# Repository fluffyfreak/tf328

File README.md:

# TF328 Revision 1

An 8mb Fast RAM + IDE Board for the CD32.

Known Issues: 

1. Your CF Card MUST be 3.3/5V tolerant as some of the control signals are 3.3V.

A prototype version was built and this contains all the lessons learned from that prototype. 

This repository contains all the files needed to produce a copy of my IDE+RAM board.

The CPLDs Required are 1 x XC9572XL-10VQ64 and 1 x XC9536XL-10VQG44C.  10ns "Commercial" version is fine.

Everything in this repository is released under the GNU GPLv2. You may create or base commercial PCBs from the work in this repository but you must make the sources for all derivative work available. I have noticed some forks have removed copyright notices. This is a breach of the GPL.

## Board Options

### Clock Buffer 

The clock buffer is a stabilty modification I added to buffer the clock due to slow rise times observed on other Amiga Hardware. It may not be required at all. If you decide not to add the clock buffer then you should jumper the middle pin of the CLOCKSEL jumper to the pin nearest the edge connector. If you wish to use the buffered clock you need to add IC9 and jumper the middle pin to the position nearest the IDE connector. If you wish to disable the board remove the jumper entirely.

### External Power

Jumper PWR1 is intended for use when bringing up the board so that the CPLDs can be programmed without inserting the card. It is not required after this unless you wish to use it to power other devices. 

### JMP Feature 

Jumper JMP is intended to trigger an NMI. This works via the MUXCPLD which detects the external pin being pulled HIGH and will pull IPL0-2 low until released. This feature is done synchronously to prevent glitches. It is intended for use with HRTMon. 

## Firmware / Requirements

  * Xilinx ISE, 14.7 (the final version - other versions may work but this is the one I support)
  * JTAG Adaptor

[For more information visit my channel](https://www.youtube.com/c/TerribleFire)

## License

This project and all the files contained are released under the GNU GPLv2. If you build a modified version of the board you must supply the end user with all the sources (this can be a web link).

# Bill of Materials

|Part | Value | Device | Package | Description |
|-----|-------|--------|---------|-------------|
| R1 | 1K | RESISTOR1206 | 1206 | Resistors | 
| R2 | 1K | RESISTOR1206 | 1206 | Resistors | 
| C1 | 10uF | CAP_CERAMIC1206 | 1206 | Ceramic Capacitors | 
| C2 | 10uF | CAP_CERAMIC1206 | 1206 | Ceramic Capacitors | 
| C3 | 10uF | CAP_CERAMIC1206 | 1206 | Ceramic Capacitors | 
| C4 | 22uF | CAP_CERAMIC1206 | 1206 | Ceramic Capacitors | 
| C5 | 100nF | CAP_CERAMIC1206 | 1206 | Ceramic Capacitors | 
| C6 | 22uF | CAP_CERAMIC1206 | 1206 | Ceramic Capacitors | 
| C7 | 1uF | CAP_CERAMIC1206 | 1206 | Ceramic Capacitors | 
| C8 | 100nF | CAP_CERAMIC1206 | 1206 | Ceramic Capacitors | 
| C9 | 100nF | CAP_CERAMIC1206 | 1206 | Ceramic Capacitors | 
| C10 | 10uF | CAP_CERAMIC1206 | 1206 | Ceramic Capacitors | 
| C11 | 22uF | CAP_CERAMIC1206 | 1206 | Ceramic Capacitors | 
| C12 | 22uF | CAP_CERAMIC1206 | 1206 | Ceramic Capacitors | 
| C13 | 22uF | CAP_CERAMIC1206 | 1206 | Ceramic Capacitors | 
| C14 | 100nF | CAP_CERAMIC1206 | 1206 | Ceramic Capacitors | 
| C15 | 100nF | CAP_CERAMIC1206 | 1206 | Ceramic Capacitors | 
| C16 | 1uF | CC0603 | C0603 | CAPACITOR, European symbol | 
| IC1 | IS41C16100C | IS41C16100C | TSOP44(50)-II |   |
| IC2 | IS41C16100C | IS41C16100C | TSOP44(50)-II |   |
| IC3 | IS41C16100C | IS41C16100C | TSOP44(50)-II |   |
| IC4 | IS41C16100C | IS41C16100C | TSOP44(50)-II |   |
| IC5 | LM1117-3.3 | V_REG_LM1117SOT223 | SOT223 | Voltage Regulator LM1117 |
| IC9 | 74LVC1G17DBV | 74LVC1G17DBV | SOT23-5 | Single Schmitt-Trigger Buffer (Optional)| 
| JMP | Optional | JUMPER-2PTH | 1X02 | NMI Jumper | 
| JP1 | CLOCKSEL | JUMPER-3PTH | 1X03 |        | 
| JTAG | JTAG | HEADER-1X6ROUND | 1X06_ROUND | PIN HEADER | 
| PWR1 | EXT5V | JUMPER-2PTH | 1X02 | Jumper | 
| MUXCPLD | XC9536XL-10VQG44C | XC9536XL-10VQG44C | SQFP-S-10X10-44 | xc9536_pc44 XC9500 In-System Programmable CPLD Family | 
| RAMCPLD | XC9572XL-10VQ64 | XC9572XL-10VQ64 | VQ64 |  
| IDECONNECTOR | 87758-4416 | 87758-4416 | 87758-4416 | 44 Pin - 2mm Dual Row Single Wafer, Vertical T/H HDR |

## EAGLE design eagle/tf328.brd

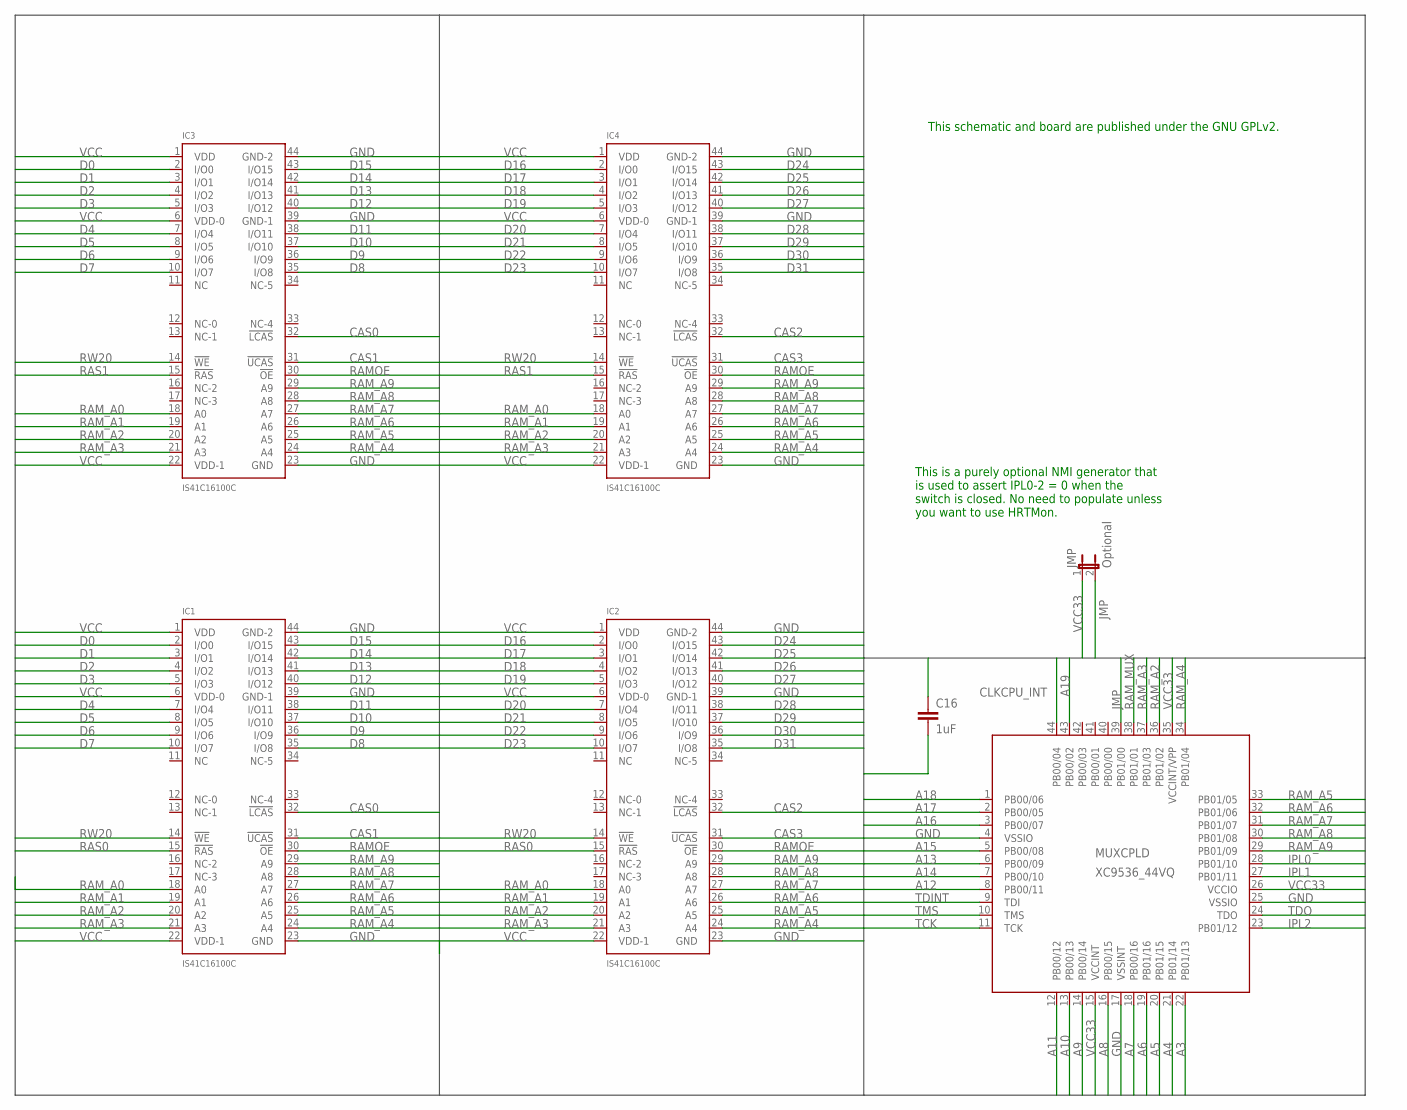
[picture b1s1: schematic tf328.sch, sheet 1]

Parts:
C16: 1uF; C0603
IC1, IC2, IC3, IC4: IS41C16100C; TSOP44(50)-II
JMP: Optional; 1X02
MUXCPLD: XC9536_44VQ; SQFP-S-10X10-44

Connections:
A3: MUXCPLD.22 (PB01/13); also elsewhere on the board
A4: MUXCPLD.21 (PB01/14); also elsewhere on the board
A5: MUXCPLD.20 (PB01/15); also elsewhere on the board
A6: MUXCPLD.19 (PB01/16); also elsewhere on the board
A7: MUXCPLD.18 (PB00/16); also elsewhere on the board
A8: MUXCPLD.16 (PB00/15); also elsewhere on the board
A9: MUXCPLD.14 (PB00/14); also elsewhere on the board
A10: MUXCPLD.13 (PB00/13); also elsewhere on the board
A11: MUXCPLD.12 (PB00/12); also elsewhere on the board
A12: MUXCPLD.8 (PB00/11); also elsewhere on the board
A13: MUXCPLD.6 (PB00/09); also elsewhere on the board
A14: MUXCPLD.7 (PB00/10); also elsewhere on the board
A15: MUXCPLD.5 (PB00/08); also elsewhere on the board
A16: MUXCPLD.3 (PB00/07); also elsewhere on the board
A17: MUXCPLD.2 (PB00/05); also elsewhere on the board
A18: MUXCPLD.1 (PB00/06); also elsewhere on the board
A19: MUXCPLD.43 (PB00/02); also elsewhere on the board
CAS0: IC1.32 (!LCAS), IC3.32 (!LCAS); also elsewhere on the board
CAS1: IC1.31 (!UCAS), IC3.31 (!UCAS); also elsewhere on the board
CAS2: IC2.32 (!LCAS), IC4.32 (!LCAS); also elsewhere on the board
CAS3: IC2.31 (!UCAS), IC4.31 (!UCAS); also elsewhere on the board
CLKCPU_INT: MUXCPLD.44 (PB00/04); also elsewhere on the board
D0: IC1.2 (I/O0), IC3.2 (I/O0); also elsewhere on the board
D1: IC1.3 (I/O1), IC3.3 (I/O1); also elsewhere on the board
D2: IC1.4 (I/O2), IC3.4 (I/O2); also elsewhere on the board
D3: IC1.5 (I/O3), IC3.5 (I/O3); also elsewhere on the board
D4: IC1.7 (I/O4), IC3.7 (I/O4); also elsewhere on the board
D5: IC1.8 (I/O5), IC3.8 (I/O5); also elsewhere on the board
D6: IC1.9 (I/O6), IC3.9 (I/O6); also elsewhere on the board
D7: IC1.10 (I/O7), IC3.10 (I/O7); also elsewhere on the board
D8: IC1.35 (I/O8), IC3.35 (I/O8); also elsewhere on the board
D9: IC1.36 (I/O9), IC3.36 (I/O9); also elsewhere on the board
D10: IC1.37 (I/O10), IC3.37 (I/O10); also elsewhere on the board
D11: IC1.38 (I/O11), IC3.38 (I/O11); also elsewhere on the board
D12: IC1.40 (I/O12), IC3.40 (I/O12); also elsewhere on the board
D13: IC1.41 (I/O13), IC3.41 (I/O13); also elsewhere on the board
D14: IC1.42 (I/O14), IC3.42 (I/O14); also elsewhere on the board
D15: IC1.43 (I/O15), IC3.43 (I/O15); also elsewhere on the board
D16: IC2.2 (I/O0), IC4.2 (I/O0); also elsewhere on the board
D17: IC2.3 (I/O1), IC4.3 (I/O1); also elsewhere on the board
D18: IC2.4 (I/O2), IC4.4 (I/O2); also elsewhere on the board
D19: IC2.5 (I/O3), IC4.5 (I/O3); also elsewhere on the board
D20: IC2.7 (I/O4), IC4.7 (I/O4); also elsewhere on the board
D21: IC2.8 (I/O5), IC4.8 (I/O5); also elsewhere on the board
D22: IC2.9 (I/O6), IC4.9 (I/O6); also elsewhere on the board
D23: IC2.10 (I/O7), IC4.10 (I/O7); also elsewhere on the board
D24: IC2.43 (I/O15), IC4.43 (I/O15); also elsewhere on the board
D25: IC2.42 (I/O14), IC4.42 (I/O14); also elsewhere on the board
D26: IC2.41 (I/O13), IC4.41 (I/O13); also elsewhere on the board
D27: IC2.40 (I/O12), IC4.40 (I/O12); also elsewhere on the board
D28: IC2.38 (I/O11), IC4.38 (I/O11); also elsewhere on the board
D29: IC2.37 (I/O10), IC4.37 (I/O10); also elsewhere on the board
D30: IC2.36 (I/O9), IC4.36 (I/O9); also elsewhere on the board
D31: IC2.35 (I/O8), IC4.35 (I/O8); also elsewhere on the board
GND: C16.2, IC1.23 (GND), IC1.39 (GND-1), IC1.44 (GND-2), IC2.23 (GND), IC2.39 (GND-1), IC2.44 (GND-2), IC3.23 (GND), IC3.39 (GND-1), IC3.44 (GND-2), IC4.23 (GND), IC4.39 (GND-1), IC4.44 (GND-2), MUXCPLD.4 (VSSIO), MUXCPLD.17 (VSSINT), MUXCPLD.25 (VSSIO); also elsewhere on the board
IPL0: MUXCPLD.28 (PB01/10); also elsewhere on the board
IPL1: MUXCPLD.27 (PB01/11); also elsewhere on the board
IPL2: MUXCPLD.23 (PB01/12); also elsewhere on the board
JMP: JMP.2, MUXCPLD.39 (PB01/00)
RAMOE: IC1.30 (!OE), IC2.30 (!OE), IC3.30 (!OE), IC4.30 (!OE); also elsewhere on the board
RAM_A0: IC1.18 (A0), IC2.18 (A0), IC3.18 (A0), IC4.18 (A0); also elsewhere on the board
RAM_A1: IC1.19 (A1), IC2.19 (A1), IC3.19 (A1), IC4.19 (A1); also elsewhere on the board
RAM_A2: IC1.20 (A2), IC2.20 (A2), IC3.20 (A2), IC4.20 (A2), MUXCPLD.36 (PB01/02)
RAM_A3: IC1.21 (A3), IC2.21 (A3), IC3.21 (A3), IC4.21 (A3), MUXCPLD.37 (PB01/03)
RAM_A4: IC1.24 (A4), IC2.24 (A4), IC3.24 (A4), IC4.24 (A4), MUXCPLD.34 (PB01/04)
RAM_A5: IC1.25 (A5), IC2.25 (A5), IC3.25 (A5), IC4.25 (A5), MUXCPLD.33 (PB01/05)
RAM_A6: IC1.26 (A6), IC2.26 (A6), IC3.26 (A6), IC4.26 (A6), MUXCPLD.32 (PB01/06)
RAM_A7: IC1.27 (A7), IC2.27 (A7), IC3.27 (A7), IC4.27 (A7), MUXCPLD.31 (PB01/07)
RAM_A8: IC1.28 (A8), IC2.28 (A8), IC3.28 (A8), IC4.28 (A8), MUXCPLD.30 (PB01/08)
RAM_A9: IC1.29 (A9), IC2.29 (A9), IC3.29 (A9), IC4.29 (A9), MUXCPLD.29 (PB01/09)
RAM_MUX: MUXCPLD.38 (PB01/01); also elsewhere on the board
RAS0: IC1.15 (!RAS), IC2.15 (!RAS); also elsewhere on the board
RAS1: IC3.15 (!RAS), IC4.15 (!RAS); also elsewhere on the board
RW20: IC1.14 (!WE), IC2.14 (!WE), IC3.14 (!WE), IC4.14 (!WE); also elsewhere on the board
TCK: MUXCPLD.11 (TCK); also elsewhere on the board
TDINT: MUXCPLD.9 (TDI); also elsewhere on the board
TDO: MUXCPLD.24 (TDO); also elsewhere on the board
TMS: MUXCPLD.10 (TMS); also elsewhere on the board
VCC: IC1.1 (VDD), IC1.6 (VDD-0), IC1.22 (VDD-1), IC2.1 (VDD), IC2.6 (VDD-0), IC2.22 (VDD-1), IC3.1 (VDD), IC3.6 (VDD-0), IC3.22 (VDD-1), IC4.1 (VDD), IC4.6 (VDD-0), IC4.22 (VDD-1); also elsewhere on the board
VCC33: C16.1, JMP.1, MUXCPLD.15 (VCCINT), MUXCPLD.26 (VCCIO), MUXCPLD.35 (VCCINT/VPP); also elsewhere on the board

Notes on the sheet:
This is a purely optional NMI generator that is used to assert IPL0-2 = 0 when the switch is closed. No need to populate unless you want to use HRTMon.
This schematic and board are published under the GNU GPLv2.

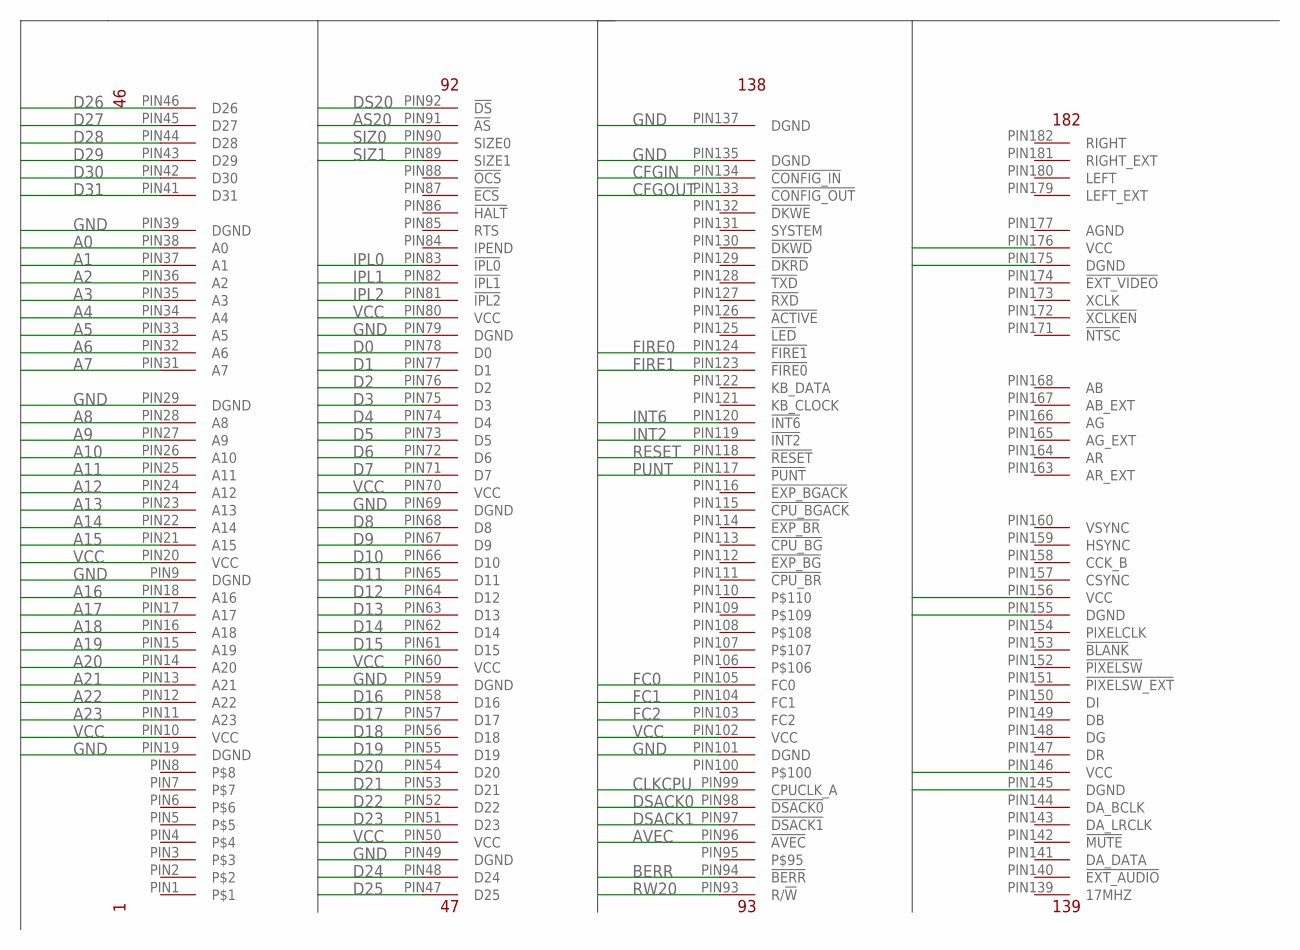
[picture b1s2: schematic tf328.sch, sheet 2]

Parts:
CONN1: MCA_CONN_182

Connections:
A0: CONN1.PIN38 (A0); also elsewhere on the board
A1: CONN1.PIN37 (A1); also elsewhere on the board
A2: CONN1.PIN36 (A2); also elsewhere on the board
A3: CONN1.PIN35 (A3); also elsewhere on the board
A4: CONN1.PIN34 (A4); also elsewhere on the board
A5: CONN1.PIN33 (A5); also elsewhere on the board
A6: CONN1.PIN32 (A6); also elsewhere on the board
A7: CONN1.PIN31 (A7); also elsewhere on the board
A8: CONN1.PIN28 (A8); also elsewhere on the board
A9: CONN1.PIN27 (A9); also elsewhere on the board
A10: CONN1.PIN26 (A10); also elsewhere on the board
A11: CONN1.PIN25 (A11); also elsewhere on the board
A12: CONN1.PIN24 (A12); also elsewhere on the board
A13: CONN1.PIN23 (A13); also elsewhere on the board
A14: CONN1.PIN22 (A14); also elsewhere on the board
A15: CONN1.PIN21 (A15); also elsewhere on the board
A16: CONN1.PIN18 (A16); also elsewhere on the board
A17: CONN1.PIN17 (A17); also elsewhere on the board
A18: CONN1.PIN16 (A18); also elsewhere on the board
A19: CONN1.PIN15 (A19); also elsewhere on the board
A20: CONN1.PIN14 (A20); also elsewhere on the board
A21: CONN1.PIN13 (A21); also elsewhere on the board
A22: CONN1.PIN12 (A22); also elsewhere on the board
A23: CONN1.PIN11 (A23); also elsewhere on the board
AGND: CONN1.PIN177 (AGND)
AS20: CONN1.PIN91 (!AS); also elsewhere on the board
AVEC: CONN1.PIN96 (!AVEC)
BERR: CONN1.PIN94 (!BERR)
CFGIN: CONN1.PIN134 (!CONFIG_IN)
CFGOUT: CONN1.PIN133 (!CONFIG_OUT)
CLKCPU: CONN1.PIN99 (CPUCLK_A); also elsewhere on the board
D0: CONN1.PIN78 (D0); also elsewhere on the board
D1: CONN1.PIN77 (D1); also elsewhere on the board
D2: CONN1.PIN76 (D2); also elsewhere on the board
D3: CONN1.PIN75 (D3); also elsewhere on the board
D4: CONN1.PIN74 (D4); also elsewhere on the board
D5: CONN1.PIN73 (D5); also elsewhere on the board
D6: CONN1.PIN72 (D6); also elsewhere on the board
D7: CONN1.PIN71 (D7); also elsewhere on the board
D8: CONN1.PIN68 (D8); also elsewhere on the board
D9: CONN1.PIN67 (D9); also elsewhere on the board
D10: CONN1.PIN66 (D10); also elsewhere on the board
D11: CONN1.PIN65 (D11); also elsewhere on the board
D12: CONN1.PIN64 (D12); also elsewhere on the board
D13: CONN1.PIN63 (D13); also elsewhere on the board
D14: CONN1.PIN62 (D14); also elsewhere on the board
D15: CONN1.PIN61 (D15); also elsewhere on the board
D16: CONN1.PIN58 (D16); also elsewhere on the board
D17: CONN1.PIN57 (D17); also elsewhere on the board
D18: CONN1.PIN56 (D18); also elsewhere on the board
D19: CONN1.PIN55 (D19); also elsewhere on the board
D20: CONN1.PIN54 (D20); also elsewhere on the board
D21: CONN1.PIN53 (D21); also elsewhere on the board
D22: CONN1.PIN52 (D22); also elsewhere on the board
D23: CONN1.PIN51 (D23); also elsewhere on the board
D24: CONN1.PIN48 (D24); also elsewhere on the board
D25: CONN1.PIN47 (D25); also elsewhere on the board
D26: CONN1.PIN46 (D26); also elsewhere on the board
D27: CONN1.PIN45 (D27); also elsewhere on the board
D28: CONN1.PIN44 (D28); also elsewhere on the board
D29: CONN1.PIN43 (D29); also elsewhere on the board
D30: CONN1.PIN42 (D30); also elsewhere on the board
D31: CONN1.PIN41 (D31); also elsewhere on the board
DS20: CONN1.PIN92 (!DS); also elsewhere on the board
DSACK0: CONN1.PIN98 (!DSACK0); also elsewhere on the board
DSACK1: CONN1.PIN97 (!DSACK1); also elsewhere on the board
FC0: CONN1.PIN105 (FC0)
FC1: CONN1.PIN104 (FC1)
FC2: CONN1.PIN103 (FC2)
FIRE0: CONN1.PIN124 (!FIRE1)
FIRE1: CONN1.PIN123 (!FIRE0)
GND: CONN1.PIN9 (DGND), CONN1.PIN19 (DGND), CONN1.PIN29 (DGND), CONN1.PIN39 (DGND), CONN1.PIN49 (DGND), CONN1.PIN59 (DGND), CONN1.PIN69 (DGND), CONN1.PIN79 (DGND), CONN1.PIN101 (DGND), CONN1.PIN135 (DGND), CONN1.PIN137 (DGND), CONN1.PIN145 (DGND), CONN1.PIN155 (DGND), CONN1.PIN175 (DGND); also elsewhere on the board
INT2: CONN1.PIN119 (!INT2); also elsewhere on the board
INT6: CONN1.PIN120 (!INT6)
IPL0: CONN1.PIN83 (!IPL0); also elsewhere on the board
IPL1: CONN1.PIN82 (!IPL1); also elsewhere on the board
IPL2: CONN1.PIN81 (!IPL2); also elsewhere on the board
PUNT: CONN1.PIN117 (!PUNT); also elsewhere on the board
RESET: CONN1.PIN118 (!RESET); also elsewhere on the board
RW20: CONN1.PIN93 (R/!W); also elsewhere on the board
SIZ0: CONN1.PIN90 (SIZE0); also elsewhere on the board
SIZ1: CONN1.PIN89 (SIZE1); also elsewhere on the board
VCC: CONN1.PIN10 (VCC), CONN1.PIN20 (VCC), CONN1.PIN50 (VCC), CONN1.PIN60 (VCC), CONN1.PIN70 (VCC), CONN1.PIN80 (VCC), CONN1.PIN102 (VCC), CONN1.PIN146 (VCC), CONN1.PIN156 (VCC), CONN1.PIN176 (VCC); also elsewhere on the board

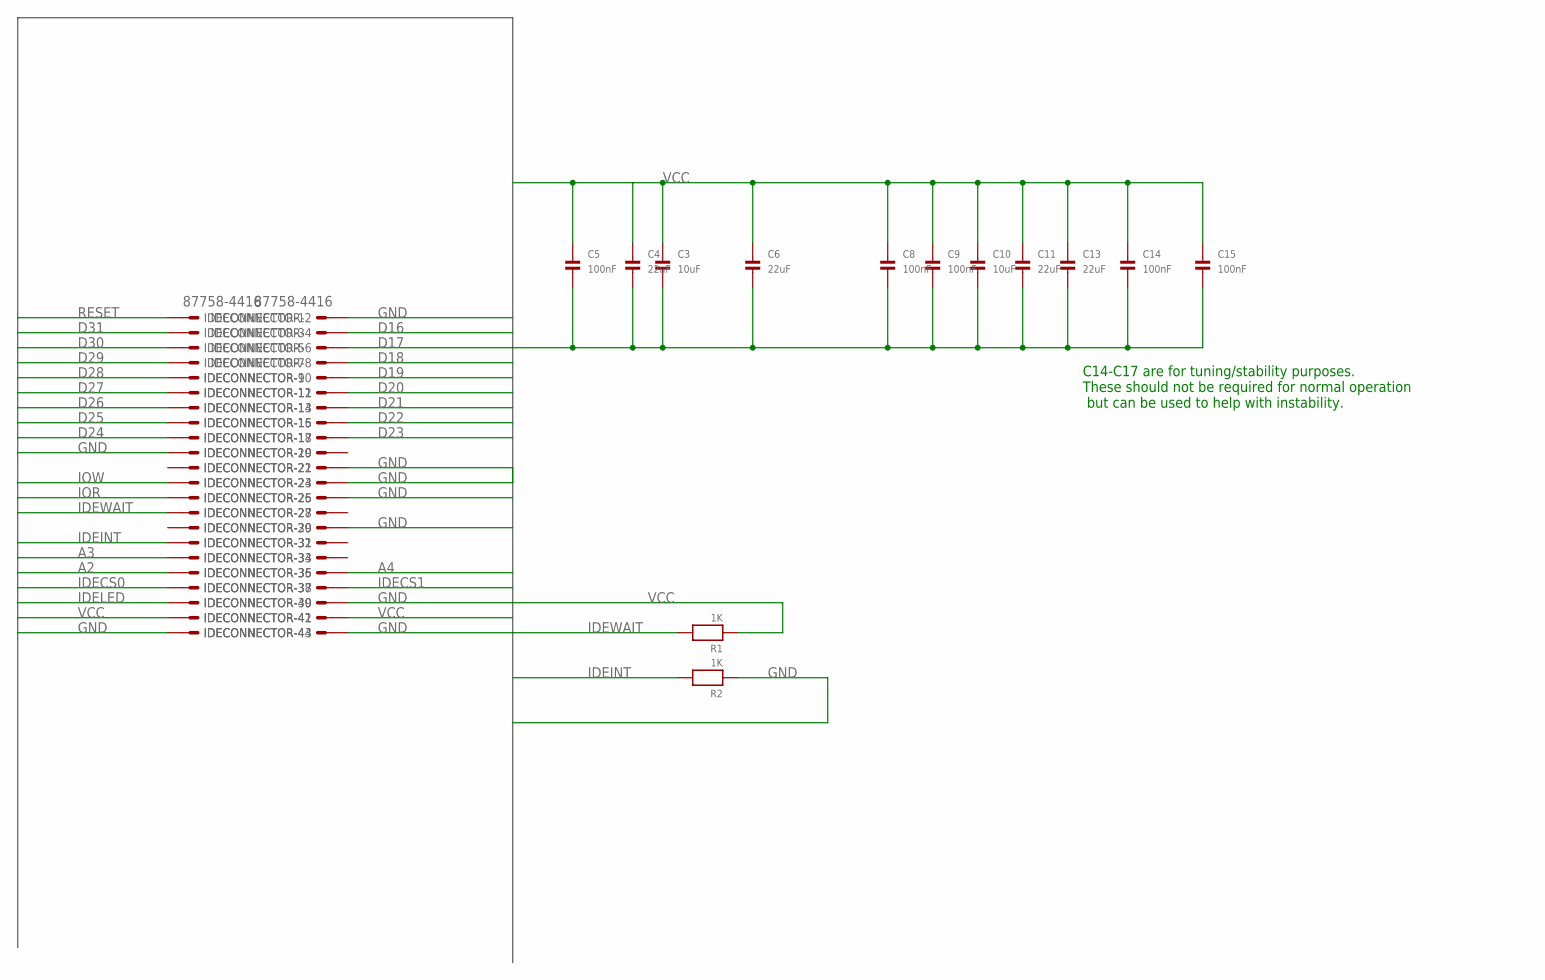
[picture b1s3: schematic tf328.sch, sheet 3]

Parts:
C3, C10: 10uF; 1206
C4, C6, C11, C13: 22uF; 1206
C5, C8, C9, C14, C15: 100nF; 1206
IDECONNECTOR: 87758-4416
R1, R2: 1K; 1206

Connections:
A2: IDECONNECTOR.35; also elsewhere on the board
A3: IDECONNECTOR.33; also elsewhere on the board
A4: IDECONNECTOR.36; also elsewhere on the board
D16: IDECONNECTOR.4; also elsewhere on the board
D17: IDECONNECTOR.6; also elsewhere on the board
D18: IDECONNECTOR.8; also elsewhere on the board
D19: IDECONNECTOR.10; also elsewhere on the board
D20: IDECONNECTOR.12; also elsewhere on the board
D21: IDECONNECTOR.14; also elsewhere on the board
D22: IDECONNECTOR.16; also elsewhere on the board
D23: IDECONNECTOR.18; also elsewhere on the board
D24: IDECONNECTOR.17; also elsewhere on the board
D25: IDECONNECTOR.15; also elsewhere on the board
D26: IDECONNECTOR.13; also elsewhere on the board
D27: IDECONNECTOR.11; also elsewhere on the board
D28: IDECONNECTOR.9; also elsewhere on the board
D29: IDECONNECTOR.7; also elsewhere on the board
D30: IDECONNECTOR.5; also elsewhere on the board
D31: IDECONNECTOR.3; also elsewhere on the board
GND: C3.2, C4.2, C5.2, C6.2, C8.2, C9.2, C10.2, C11.2, C13.2, C14.2, C15.2, IDECONNECTOR.2, IDECONNECTOR.19, IDECONNECTOR.22, IDECONNECTOR.24, IDECONNECTOR.26, IDECONNECTOR.30, IDECONNECTOR.40, IDECONNECTOR.43, IDECONNECTOR.44, R2.1; also elsewhere on the board
IDECS0: IDECONNECTOR.37; also elsewhere on the board
IDECS1: IDECONNECTOR.38; also elsewhere on the board
IDEINT: IDECONNECTOR.31, R2.2; also elsewhere on the board
IDELED: IDECONNECTOR.39
IDEWAIT: IDECONNECTOR.27, R1.2
IOR: IDECONNECTOR.25; also elsewhere on the board
IOW: IDECONNECTOR.23; also elsewhere on the board
RESET: IDECONNECTOR.1; also elsewhere on the board
VCC: C3.1, C4.1, C5.1, C6.1, C8.1, C9.1, C10.1, C11.1, C13.1, C14.1, C15.1, IDECONNECTOR.41, IDECONNECTOR.42, R1.1; also elsewhere on the board

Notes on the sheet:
C14-C17 are for tuning/stability purposes. These should not be required for normal operation but can be used to help with instability.

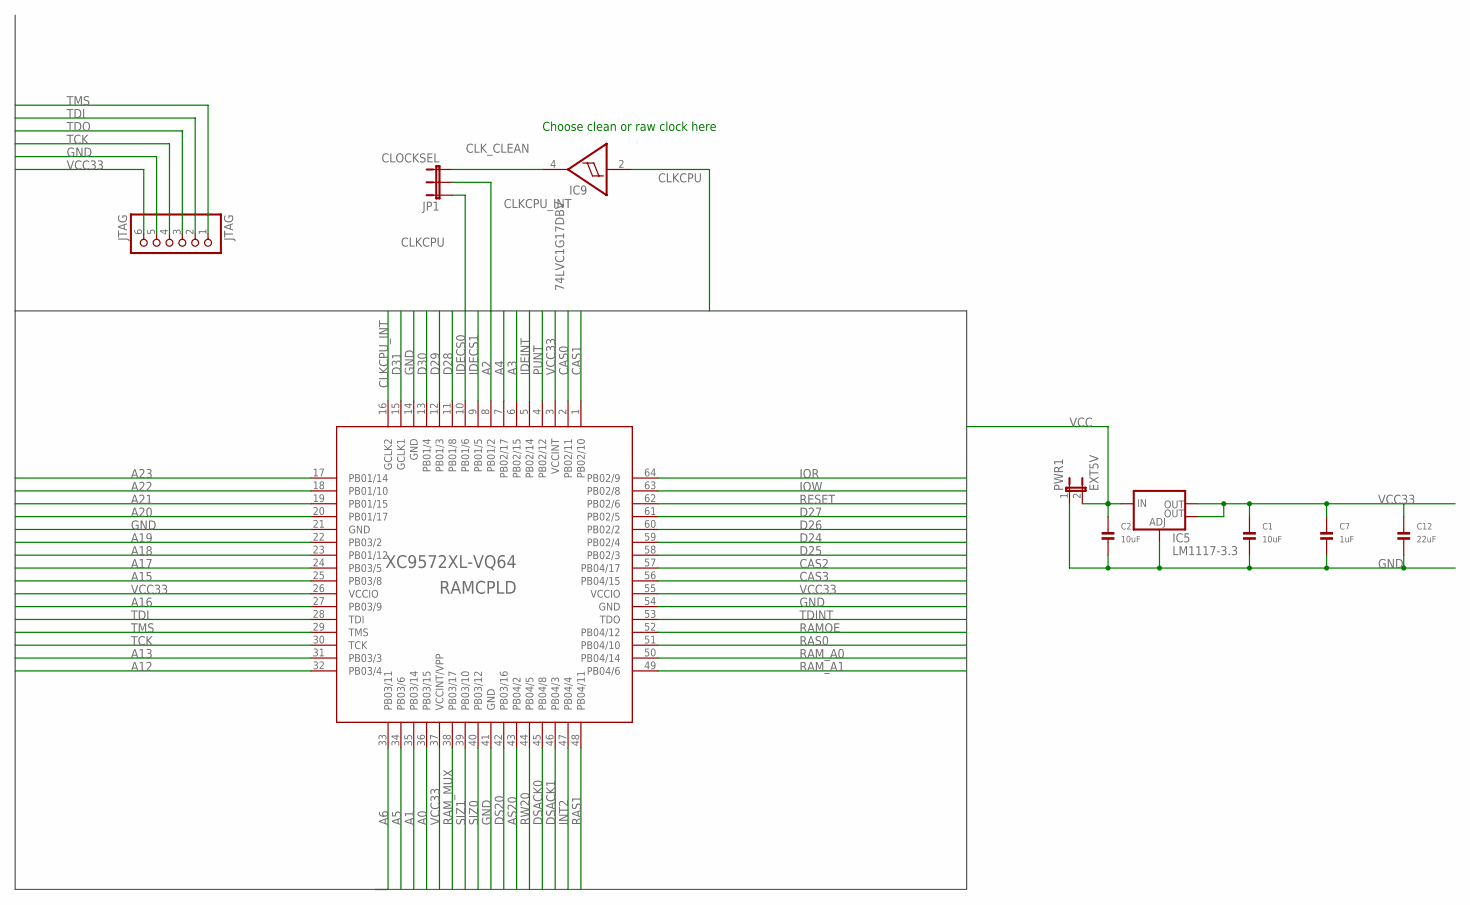
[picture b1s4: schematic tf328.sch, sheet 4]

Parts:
C1, C2: 10uF; 1206
C7: 1uF; 1206
C12: 22uF; 1206
IC5: LM1117-3.3; SOT223
IC9: 74LVC1G17DBV; SOT23-5
JP1: CLOCKSEL; 1X03
JTAG: JTAG; 1X06_ROUND
PWR1: EXT5V; 1X02
RAMCPLD: XC9572XL-VQ64; VQ64

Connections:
A0: RAMCPLD.36 (PB03/15); also elsewhere on the board
A1: RAMCPLD.35 (PB03/14); also elsewhere on the board
A2: RAMCPLD.8 (PB01/2); also elsewhere on the board
A3: RAMCPLD.6 (PB02/15); also elsewhere on the board
A4: RAMCPLD.7 (PB02/17); also elsewhere on the board
A5: RAMCPLD.34 (PB03/6); also elsewhere on the board
A6: RAMCPLD.33 (PB03/11); also elsewhere on the board
A12: RAMCPLD.32 (PB03/4); also elsewhere on the board
A13: RAMCPLD.31 (PB03/3); also elsewhere on the board
A15: RAMCPLD.25 (PB03/8); also elsewhere on the board
A16: RAMCPLD.27 (PB03/9); also elsewhere on the board
A17: RAMCPLD.24 (PB03/5); also elsewhere on the board
A18: RAMCPLD.23 (PB01/12); also elsewhere on the board
A19: RAMCPLD.22 (PB03/2); also elsewhere on the board
A20: RAMCPLD.20 (PB01/17); also elsewhere on the board
A21: RAMCPLD.19 (PB01/15); also elsewhere on the board
A22: RAMCPLD.18 (PB01/10); also elsewhere on the board
A23: RAMCPLD.17 (PB01/14); also elsewhere on the board
AS20: RAMCPLD.43 (PB04/2); also elsewhere on the board
CAS0: RAMCPLD.2 (PB02/11); also elsewhere on the board
CAS1: RAMCPLD.1 (PB02/10); also elsewhere on the board
CAS2: RAMCPLD.57 (PB04/17); also elsewhere on the board
CAS3: RAMCPLD.56 (PB04/15); also elsewhere on the board
CLKCPU: IC9.2 (I), JP1.1; also elsewhere on the board
CLKCPU_INT: JP1.2, RAMCPLD.16 (GCLK2); also elsewhere on the board
CLK_CLEAN: IC9.4 (O), JP1.3
D24: RAMCPLD.59 (PB02/4); also elsewhere on the board
D25: RAMCPLD.58 (PB02/3); also elsewhere on the board
D26: RAMCPLD.60 (PB02/2); also elsewhere on the board
D27: RAMCPLD.61 (PB02/5); also elsewhere on the board
D28: RAMCPLD.11 (PB01/8); also elsewhere on the board
D29: RAMCPLD.12 (PB01/3); also elsewhere on the board
D30: RAMCPLD.13 (PB01/4); also elsewhere on the board
D31: RAMCPLD.15 (GCLK1); also elsewhere on the board
DS20: RAMCPLD.42 (PB03/16); also elsewhere on the board
DSACK0: RAMCPLD.45 (PB04/8); also elsewhere on the board
DSACK1: RAMCPLD.46 (PB04/3); also elsewhere on the board
GND: C1.2, C2.2, C7.2, C12.2, IC5.1 (ADJ), IC9.3 (GND), JTAG.5, PWR1.1, RAMCPLD.14 (GND), RAMCPLD.21 (GND), RAMCPLD.41 (GND), RAMCPLD.54 (GND); also elsewhere on the board
IDECS0: RAMCPLD.10 (PB01/6); also elsewhere on the board
IDECS1: RAMCPLD.9 (PB01/5); also elsewhere on the board
IDEINT: RAMCPLD.5 (PB02/14); also elsewhere on the board
INT2: RAMCPLD.47 (PB04/4); also elsewhere on the board
IOR: RAMCPLD.64 (PB02/9); also elsewhere on the board
IOW: RAMCPLD.63 (PB02/8); also elsewhere on the board
PUNT: RAMCPLD.4 (PB02/12); also elsewhere on the board
RAMOE: RAMCPLD.52 (PB04/12); also elsewhere on the board
RAM_A0: RAMCPLD.50 (PB04/14); also elsewhere on the board
RAM_A1: RAMCPLD.49 (PB04/6); also elsewhere on the board
RAM_MUX: RAMCPLD.38 (PB03/17); also elsewhere on the board
RAS0: RAMCPLD.51 (PB04/10); also elsewhere on the board
RAS1: RAMCPLD.48 (PB04/11); also elsewhere on the board
RESET: RAMCPLD.62 (PB02/6); also elsewhere on the board
RW20: RAMCPLD.44 (PB04/5); also elsewhere on the board
SIZ0: RAMCPLD.40 (PB03/12); also elsewhere on the board
SIZ1: RAMCPLD.39 (PB03/10); also elsewhere on the board
TCK: JTAG.4, RAMCPLD.30 (TCK); also elsewhere on the board
TDI: JTAG.2, RAMCPLD.28 (TDI)
TDINT: RAMCPLD.53 (TDO); also elsewhere on the board
TDO: JTAG.3; also elsewhere on the board
TMS: JTAG.1, RAMCPLD.29 (TMS); also elsewhere on the board
VCC: C2.1, IC5.3 (IN), IC9.5 (VCC), PWR1.2; also elsewhere on the board
VCC33: C1.1, C7.1, C12.1, IC5.2 (OUT), IC5.4 (OUT), JTAG.6, RAMCPLD.3 (VCCINT), RAMCPLD.26 (VCCIO), RAMCPLD.37 (VCCINT/VPP), RAMCPLD.55 (VCCIO); also elsewhere on the board

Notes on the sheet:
Choose clean or raw clock here

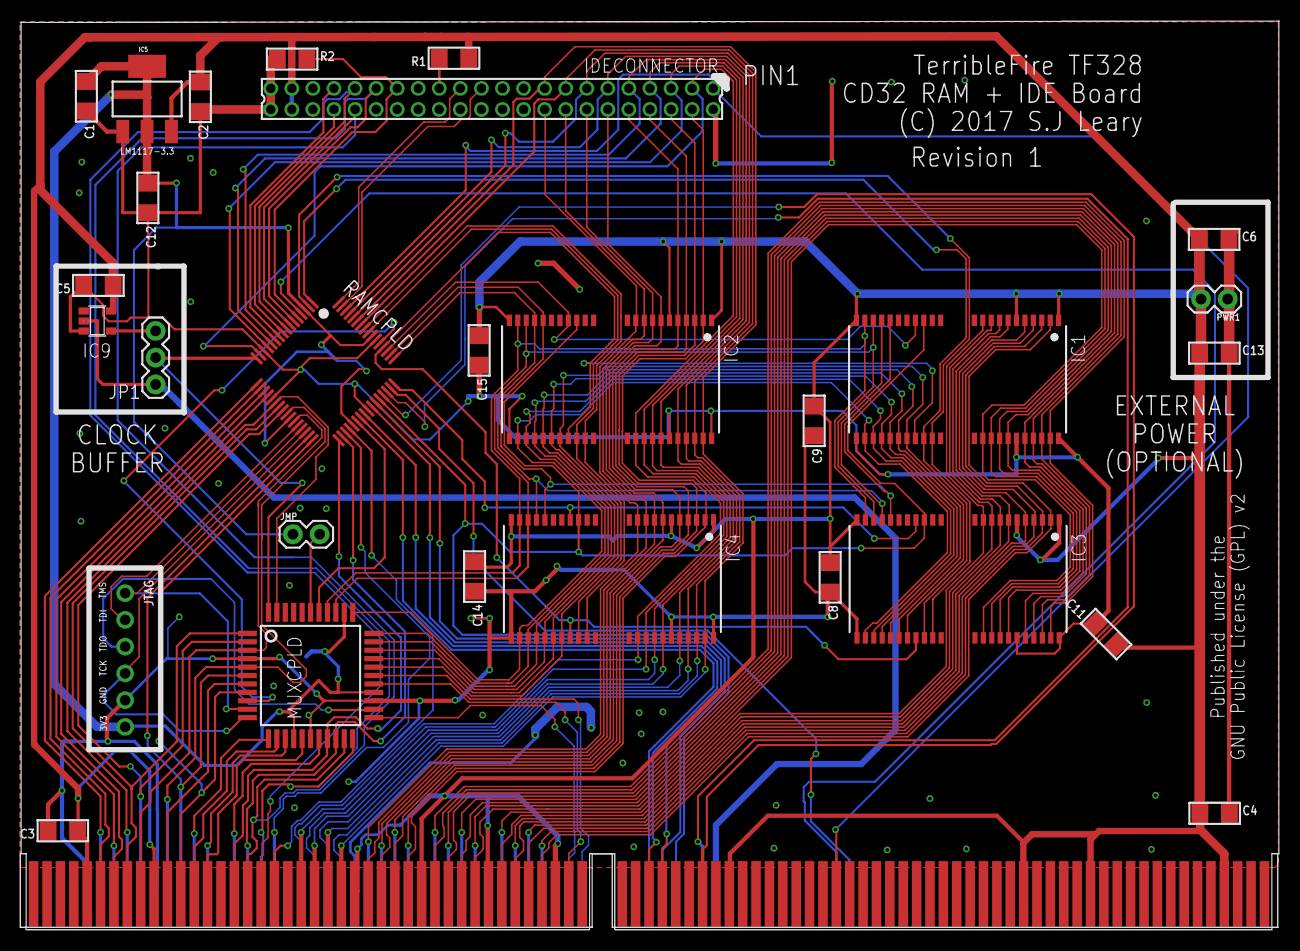
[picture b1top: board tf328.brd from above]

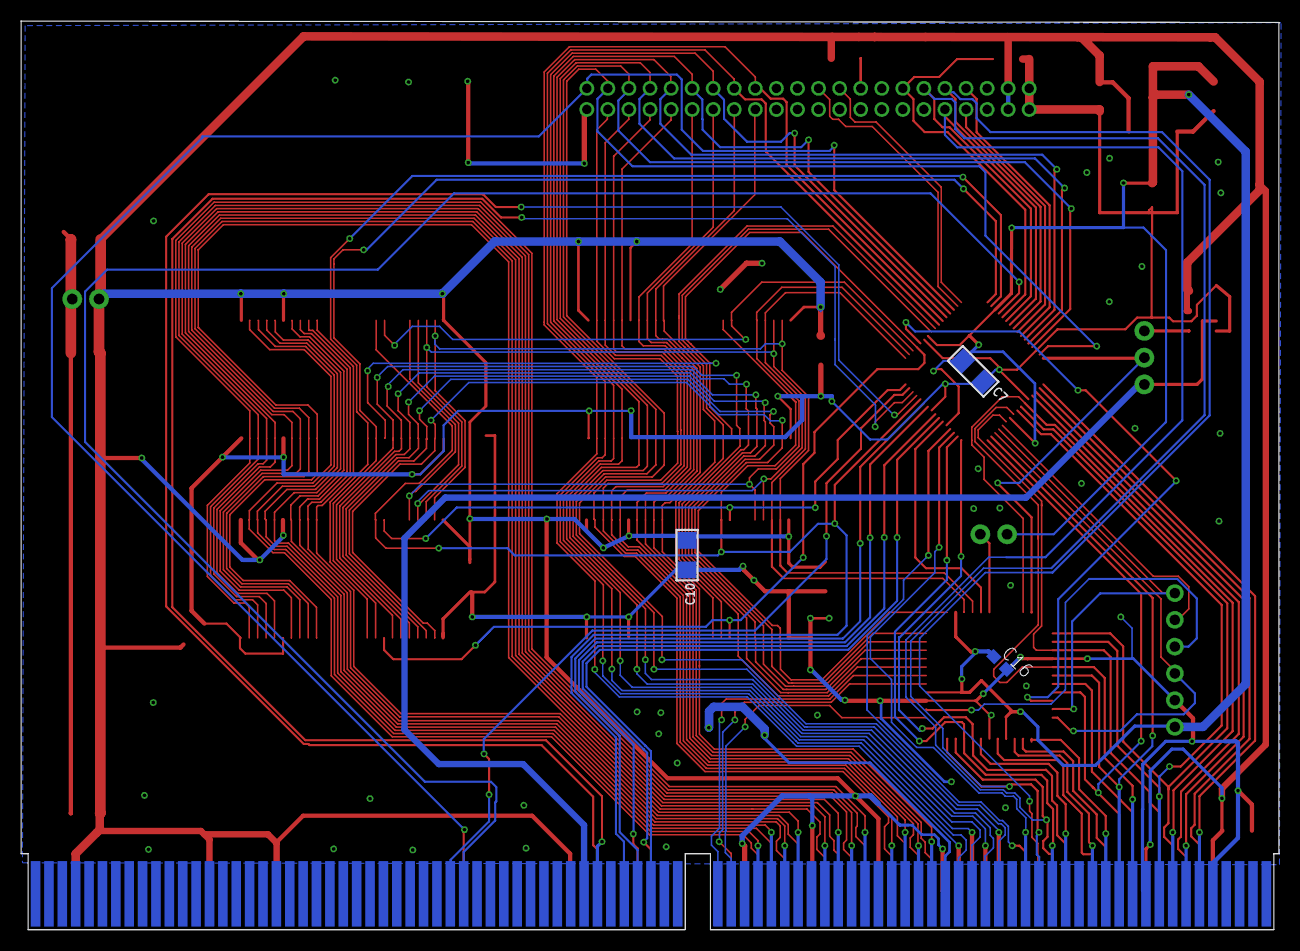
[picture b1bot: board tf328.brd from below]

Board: 2 copper layers, 119.4 x 86.3 mm, 32 parts (3 on the bottom side), 105 nets.

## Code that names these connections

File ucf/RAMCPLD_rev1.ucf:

# Copyright (C) 2016-2017, Stephen J. Leary
# All rights reserved.
#
# This file is part of TF530 (Terrible Fire 030 Accelerator)
#
# TF530 is free software: you can redistribute it and/or modify
# it under the terms of the GNU General Public License as published by
# the Free Software Foundation, either version 3 of the License, or
# (at your option) any later version.
#
# TF530 is distributed in the hope that it will be useful,
# but WITHOUT ANY WARRANTY; without even the implied warranty of
# MERCHANTABILITY or FITNESS FOR A PARTICULAR PURPOSE.  See the
# GNU General Public License for more details.
#
# You should have received a copy of the GNU General Public License
# along with TF530. If not, see <http://www.gnu.org/licenses/>.

NET "A<0>"      LOC="36";
NET "A<1>"      LOC="35";
NET "A<2>"      LOC="8";
NET "A<3>"      LOC="6";
NET "A<4>"      LOC="7";
NET "A<5>"      LOC="34";
NET "A<6>"      LOC="33";
NET "A<12>"      LOC="32";
NET "A<13>"      LOC="31";
NET "A<15>"      LOC="25";
NET "A<16>"      LOC="27";
NET "A<17>"      LOC="24";
NET "A<18>"      LOC="23";
NET "A<19>"      LOC="22";
NET "A<20>"      LOC="20";
NET "A<21>"      LOC="19";
NET "A<22>"      LOC="18";
NET "A<23>"      LOC="17";
NET "AS20"      LOC="43";
NET "CAS<0>"      LOC="2";
NET "CAS<1>"      LOC="1";
NET "CAS<2>"      LOC="57";
NET "CAS<3>"      LOC="56";
NET "CLKCPU"      LOC="16";
NET "D<0>"      LOC="59";
NET "D<1>"      LOC="58";
NET "D<2>"      LOC="60";
NET "D<3>"      LOC="61";
NET "D<4>"      LOC="11";
NET "D<5>"      LOC="12";
NET "D<6>"      LOC="13";
NET "D<7>"      LOC="15";
NET "DS20"      LOC="42";
NET "DSACK<0>"      LOC="45";
NET "DSACK<1>"      LOC="46";
NET "IDECS<0>"      LOC="10";
NET "IDECS<1>"      LOC="9";
NET "IDEINT"      LOC="5";
NET "INT2"      LOC="47";
NET "IOR"      LOC="64";
NET "IOW"      LOC="63";
NET "PUNT"      LOC="4";
NET "RAMOE"      LOC="52";
NET "RAM_A<0>"      LOC="50";
NET "RAM_A<1>"      LOC="49";
NET "RAM_MUX"      LOC="38";
NET "RAS<0>"      LOC="51";
NET "RAS<1>"      LOC="48";
NET "RESET"      LOC="62";
NET "RW20"      LOC="44";
NET "SIZ<0>"      LOC="40";
NET "SIZ<1>"      LOC="39";

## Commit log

2017-07-28 Initial commit of the board.
2017-07-28 Create LICENSE
2017-07-30 Adding an image of the board
2017-07-30 adding images
2017-08-09 Working update.
2017-08-09 jed files and sources
2017-10-02 Idea i had to make the board be disabled if the clock is not present. Hold everything in POR mode until i see three clock edges.
2017-10-02 Read for test.
    Works for me on the boot menu.
2017-10-02 removed some test code
2017-10-07 new timer changes.
2017-10-07 updating the firmware with the refresh timer.
2017-10-08 Commiting the refresh timer firmware
2017-10-08 Commiting the binaries for this branch
2018-01-06 Merging in contributed code
2018-01-06 Adding the ata.v from the tf530. More hard disks will now work
2018-01-06 Comming the binaries
2018-01-06 creating a branch for 1WS ide
2018-10-18 creating a new branch for non-ide boards (A1200s)

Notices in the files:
eagle/tf328.brd:
(C) 2017 S.J Leary
GNU Public License (GPL) v2
parts and their libraries:
microbuilder: This work is placed in the public domain, and may be freely used for commercial and non-commercial work with the following conditions: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
SparkFun-Retired: Licensing:Creative Commons ShareAlike 4.0 International - https://creativecommons.org/licenses/by-sa/4.0
